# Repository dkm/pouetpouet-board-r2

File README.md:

# PouetPouet

The firmware is [Keyberon](https://github.com/TeXitoi/keyberon), a
pure rust firmware.

The goal was:
* build a custom keyboard from scratch
* continue to learn embedded rust
* have fun

## Features

 * ortholinear
 * 60 keys, using Cherry MX switches, only 1U keycaps;
 * 4 RGB LEDs for status;
 * 6 RGB LEDs for backlight;
 * USB-C connector;
 * 1 STM32F072 MCU, with hardware USB DFU bootloader;
 * Only onboard SMD component (except for the switches).
 * ESD protection

## Inspiration

 * [Keyseebee](https://github.com/TeXitoi/keyseebee) for being the «I will
   change it quickly and have something ready in an hour» base project (even if
   I ended up redoing most of the hardware design). It was really nice to have a
   solid base to learn and bootstrap the project.
 * [Typematrix 2030](http://typematrix.com/2030/features.php): I own 2 of them
   and really love them. But both are getting old and some keys are not working
   correctly (this motivated the keyboard change).
 * [Steamvan](https://github.com/jmdaly/steamvan) for some KiCad design ideas;
 * [Preonic](https://olkb.com/collections/preonic) as a model: ortholinear, good
   balance between size/usability, simple.

## Usefull resources
 * [Mechanical Keyboard](https://github.com/help-14/mechanical-keyboard) is a list of DIY keyboards
 * [Awesome Mechanical Keyboard](https://github.com/BenRoe/awesome-mechanical-keyboard) is another [«awesome»](https://github.com/topics/awesome) list
 * [Masterzen](http://www.masterzen.fr/2020/05/03/designing-a-keyboard-part-1/)
   and many others for writing online tutorials for newbies like me.

## Build log

Disclaimer: I'm a software developper, this is my first real PCB design and my first try at SMD soldering: do not take anything here for granted :)

The project started as a quick-hack of Keyseebee to make it simpler but ended up
as a near full redesign. As every DIY project, the goal was to be quick and
simple (spoiler: it was neither).

Half of the parts have been soldered with a soldering iron (TS80P), the other
half with hot air station. Clearly, with my [un]existing soldering skills, the
hot air is a huge win. But I think I would have simply spent more time by only
using the iron. Even the small sod-323 diodes without the `_handsoldering` pads
(mistake) were not a real problem (tricky, but even I could do it). For
reference, I have soldered all SMD components for the second board under 2 hours
with hot air.

The trickiest
part is the USB connector if you don't have a hot air station: the plastic
casing melts with the solder.

* The LEDs are mostly optional, and the 6 used for the backlight are nearly
  useless. I did not really study how to insert LEDs for a nice backlight and the
  result is not really satisfactory.
* I'll hopefully find time to use plexiglass plate to put below the PCB and
  above the visible part. I've added holes for this but never really planed
  anything really. If you really want something nice here, you may check this
  before.

## Layout

As a typematrix user, I really like the middle column with `backspace/enter/del`
so naturaly I've tried to do something similar. The [initial
layout](http://www.keyboard-layout-editor.com/##@_pcb:true%3B&@_c=%238f00ff&sm=cherry&sb=gateron%3B&=F2%0A%0A%0A%E2%80%94%0A%0A%0A%0A%0A%0A1%0A%22&=F3%0A%0A%0A%3C%0A%0A%0A%0A%0A%0A2%0A%C2%AB&=F4%0A%0A%0A%3E%0A%0A%0A%0A%0A%0A3%0A%C2%BB&=F5%0A%0A%0A%5B%0A%0A%0A%0A%0A%0A4%0A(&=F6%0A%0A%0A%5D%0A%0A%0A%0A%0A%0A5%0A)&_c=%23cf94ff%3B&=F1%0A%0A%0A%0A%0A%0A%0A%0A%0A%23%0A$&_c=%238f00ff%3B&=F7%0A%0A%0A%0A%0A%0A%0A%0A%0A6%0A%2F@&=F8%0A%0A%0A%0A%0A%0A%0A%0A%0A7%0A+&=F9%0A%0A%0A%0A%0A%0A%0A%0A%0A8%0A-&=F10%0A%0A%0A%0A%0A%0A%0A%0A%0A9%0A%2F%2F&=F11%0A%0A%0A%0A%0A%0A%0A%0A%0A0%0A*&_c=%23cf94ff%3B&=F12%0A%0A%0A%0A%0A%0A%0A%0A%0A%C2%B0%0A%2F=%3B&@_c=%234bfad0%3B&=PrtScr%0A%0A%0A%7C%0A%0A%0A%0A%0A%0AB&=VerNum%0A%0A%0A%0A%0A%0A%0A%0A%0A%C3%89&=%0A%0A%0A%2F&%0A%0A%0A%0A%0A%0AP&=%0A%0A%0A%C5%93%0A%0A%0A%0A%0A%0AO&_a:7%3B&=%C3%88&_c=%23fcc0c0&a:4%3B&=Esc%0A%0A%0A%0A%0A%0A%0A%0A%0ATab&_c=%23dbfff7%3B&=Ins%0A%0A%0A%0A%0A%0A%0A%0A%0A!%0A%5E&_c=%234bfad0%3B&=%2F&uArr%2F%3B%0A%0A%0A%0A%0A%0A%0A%0A%0AV&=%2F&dArr%2F%3B%0A%0A%0A%0A%0A%0A%0A%0A%0AD&=7%0A%0A%0A%0A%0A%0A%0A%0A%0AL&=8%0A%0A%0A%0A%0A%0A%0A%0A%0AJ&=9%0A%0A%0A%0A%0A%0A%0A%0A%0AZ%3B&@=%0A%0A%0A%C3%A6%0A%0A%0A%0A%0A%0AA&=%0A%0A%0A%C3%B9%0A%0A%0A%0A%0A%0AU&=%0A%0A%0A%22%0A%0A%0A%0A%0A%0AI&=%0A%0A%0A%E2%82%AC%0A%0A%0A%0A%0A%0AE&_c=%23dbfff7&a:5%3B&=%0A,%0A%0A%0A%0A%0A%2F%3B&_c=%23fcc0c0&a:7%3B&=%3Ci%20class%2F='mss%20mss-Unicode-BackSpace-DeleteLeft-Big-2'%3E%3C%2F%2Fi%3E&_c=%234bfad0&a:4%3B&=%3Ci%20class%2F='kb%20kb-Arrows-Top-2'%3E%3C%2F%2Fi%3E%0A%0A%0A%0A%0A%0A%0A%0A%0AC&=%2F&uarr%2F%3B%0A%0A%0A%0A%0A%0A%0A%0A%0AT&=%3Ci%20class%2F='kb%20kb-Arrows-Bottom-2'%3E%3C%2F%2Fi%3E%0A%0A%0A%0A%0A%0A%0A%0A%0AS&=4%0A%0A%0A%0A%0A%0A%0A%0A%0AR&=5%0A%0A%0A%0A%0A%0A%0A%0A%0AN&=6%0A%0A%0A%0A%0A%0A%0A%0A%0AM%3B&@=%C3%8A%0A%0A%0A%5C%0A%0A%0A%0A%0A%0A%C3%80&=%3Ci%20class%2F='fa%20fa-rotate-left'%3E%3C%2F%2Fi%3E%0A%0A%0A%7B%0A%0A%0A%0A%0A%0AY&=%3Ci%20class%2F='fa%20fa-plus'%3E%3C%2F%2Fi%3E%0A%0A%0A%7D%0A%0A%0A%0A%0A%0AX&_c=%23dbfff7%3B&=%3Ci%20class%2F='fa%20fa-minus'%3E%3C%2F%2Fi%3E%0A%0A%0A%E2%80%A6%0A%0A%0A%0A%0A%0A%2F:%0A.&_c=%234bfad0%3B&=%0A%0A%0A~%0A%0A%0A%0A%0A%0AK&_c=%23fcc0c0&a:7%3B&=%2F&crarr%2F%3B&_c=%23dbfff7&a:4%3B&=%2F&larr%2F%3B%0A%0A%0A%0A%0A%0A%0A%0A%0A%3F%0A'&_c=%234bfad0%3B&=%2F&darr%2F%3B%0A%0A%0A%0A%0A%0A%0A%0A%0AQ&=%2F&rarr%2F%3B%0A%0A%0A%0A%0A%0A%0A%0A%0AG&=1%0A%0A%0A%0A%0A%0A%0A%0A%0AH&=2%0A%0A%0A%0A%0A%0A%0A%0A%0AF&=3%0A%0A%0A%0A%0A%0A%0A%0A%0A%C3%87%3B&@_c=%23ff59d1&a:7%3B&=Ctrl&_c=%238f00ff%3B&=%2F&uArr%2F%3B&=Win&_c=%231500ff&a:4%3B&=%3Ci%20class%2F='fa%20fa-lightbulb-o'%3E%3C%2F%2Fi%3E%0A%0A%0A%0A%0A%0A%0A%0A%0AShift&_c=%238f00ff&a:7%3B&=Alt&_c=%23fcc0c0&a:4%3B&=%0A%0A%0A%2F_%0A%0A%0A%0A%0A%0Anbspc%0Aspc&_c=%238f00ff&a:7%3B&=AltGr&_c=%234bfad0&a:4%3B&=0%0A%0A%0A%0A%0A%0A%0A%0A%0AW&_c=%23dbfff7&a:5%3B&=%0A%25%0A%0A%0A%0A%0A%60&_c=%238f00ff&a:7%3B&=Del&_c=%231500ff%3B&=Shift&_c=%23ff59d1%3B&=Ctrl) has only the `%` and `w` key at different locations:

You can also see how the LEDs are currently used. It's mostly useless/for fun. They may be used someday to measure typing speed or do something else, but in the meantime, they blink like this:

## Bill Of Materials

|Item                                                                      |Package|Qty|Remarks                                |Price |
|--------------------------------------------------------------------------|-------|--:|---------------------------------------|-----:|
| PCB                                                                      |       | 1 | [aisler](https://aisler.net/p/BWUOMHHS) (by 3 mini) |  28.80€  |
| 100 nF                                                                   | 0805  | 5 |  aisler*                                 | 0€    |
| PRTR5V0U2X,215                                                           | sot-143| 1 | aisler*                                 | 0.43€ |
| 4.7 uF                                                                   | 0805  | 2 |  aisler*                                 | 0€    |
| 470 Ohm                                                                  | 0805  | 1 |  aisler*                                 | 0€    |
| TLV70233DBVR                                                             | sot-23| 1 |  aisler*                                 | 0.37€ |
| 74LVC1G34GW,125                                                          |       | 1 |  aisler*                                 | 0.28€ |
| 0805L050WR (500mA Polyfuse)                                              | 0805  | 1 |  aisler*                                 | 1.91€ |
| RS282G05A3SMRT (micro switch)                                            |       | 2 |  aisler*                                 | 1.26€ |
| 100nF                                                                    | 0805  | 2 |  aisler*                                 | 0€ |
| 5.1 kOhm                                                                 | 0805  | 3 |  aisler*                                 | 0€ |
| 0805L050WR (500mA Polyfuse)                                              | 0805  | 1 |  aisler*                                 | 0€ |
| [1N4148WS-7-F](https://fr.rs-online.com/web/p/diodes-de-commutation/7384737/) | sod-323 | 60|   rs-online (by 200)                  | 3.24€  |
| [WS2812B](https://www.aliexpress.com/item/4000750610574.html?spm=a2g0s.9042311.0.0.27424c4dS3DGkH) |       | 10|                                       | 1€  |
| [USB TypeC HRO Receptacle](https://www.aliexpress.com/item/33056042016.html?spm=a2g0s.9042311.0.0.1d8b4c4d8WcR7j) |       | 1 |  by 10 mini   | 0.25€  |
| [Gateron Switch 5-pin](https://fr.aliexpress.com/item/32797603005.html?spm=a2g0s.9042311.0.0.72906c37zAMdzk) |       | 60| by 65                                   | 15.24€ |
| [Blank DSA Keycaps](https://fr.aliexpress.com/item/32850729893.html?spm=a2g0s.9042311.0.0.3c4b6c37vkQ3vr)    |       | 60| by 200                                   | 15.6€  |
| [STM32F072CBT6](https://fr.aliexpress.com/item/4000419148272.html?spm=a2g0s.9042311.0.0.43286c37wfyZHW)      | LQFP48 | 1 |                                         | 2.87€ | 
|--------------------------------------------------------------------------|-------|--:|------------------------------------------|------|
|[TPS2553DBVR-1](https://www.digikey.fr/fr/products/detail/texas-instruments/TPS2553DBVR-1/5143873) | PKG? | 1 | FIND | ??€|
|[SK6812-Mini]() | PGK? | 60+4 | FIND | ??€ |
| 100nF                                                                    | 0805  | 2 |  aisler*                                 | 0€ |
| 9.1 kOhm                                                                 | 0805  | 4 |  aisler*                                 | 0€ |
| 68 kOhm                                                                  | 0805  | 6 |  aisler*                                 | 0€ |
|[2N7002](https://www.digikey.fr/fr/products/detail/stmicroelectronics/2N7002/654418) | SOT23-3 | 2 | FIND | ?€ |
| 100uF  | 6032 | 1 | FIND | ??€ |

The total for 3 keyboard is 71.25€. Beware that some parts can't be ordered for
the exact amount and you need to buy more (in particular, aisler won't do
anything under 3 units, so you need to spend at least ~90€ for 3 PCBs).

*: Bought using magic match from Aisler. Some components are then
 «free» (resistor, capacitor) and some are not.

## Compiling and flashing

Install the complete toolchain and utils:

```shell
curl https://sh.rustup.rs -sSf | sh
rustup target add thumbv6m-none-eabi
rustup component add llvm-tools-preview
cargo install cargo-binutils
sudo apt-get install dfu-util
```

Compile:

Do not omit the `--release` as the debug code will not fit in the memory (the
linker will raise an error).

```shell
cd firmware
cargo objcopy --bin pouetpouet --release -- -O binary pouetpouet.bin
```

To flash using dfu-util, first put the board in dfu mode by pressing
BOOT, pressing and releasing RESET and releasing BOOT. Then:

```shell
dfu-util -d 0483:df11 -a 0 -s 0x08000000:leave -D pouetpouet.bin
```

The fist time, if the write fail, your flash might be protected. To
unprotect:

```shell
dfu-util -d 0483:df11 -a 0 -s 0x08000000:force:unprotect -D pouetpouet.bin
```

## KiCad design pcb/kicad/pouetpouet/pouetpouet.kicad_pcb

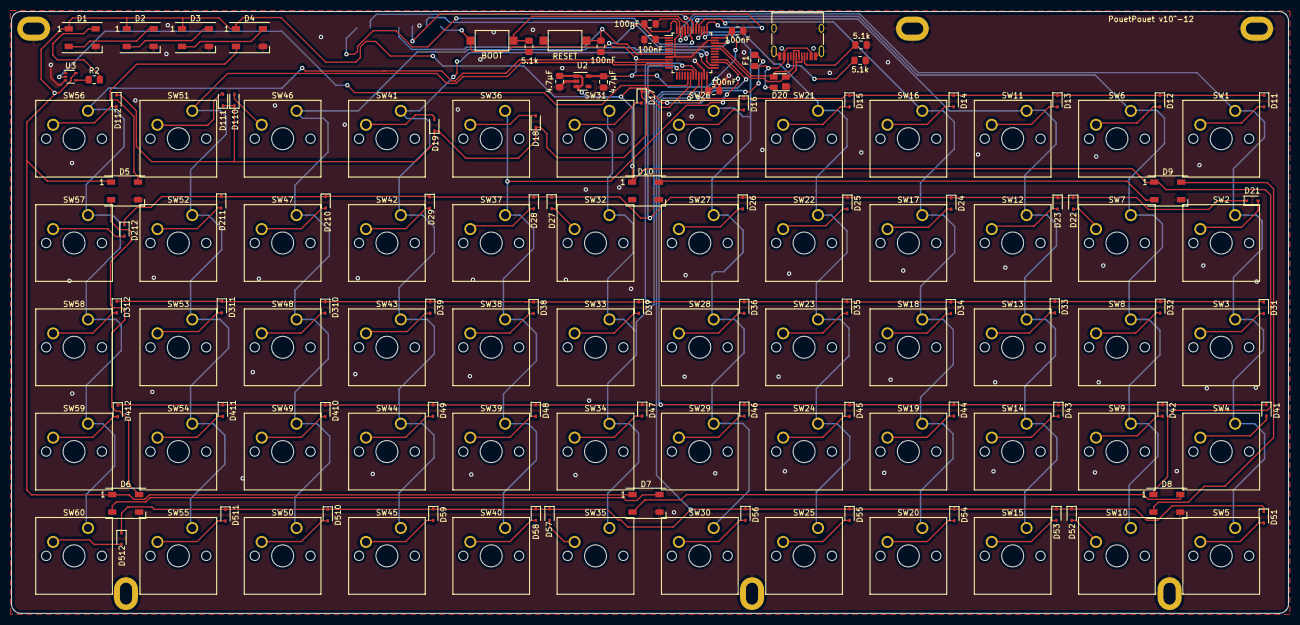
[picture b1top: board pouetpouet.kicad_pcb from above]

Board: 2 copper layers, 232.6 x 109.6 mm, 156 parts (1 on the bottom side), 103 nets.

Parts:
C1, C2, C3, C4, C5: 100nF; C_0805_2012Metric_Pad1.15x1.40mm_HandSolder
C6, C7: 4.7µF; C_0805_2012Metric_Pad1.15x1.40mm_HandSolder
D1, D2, D3, D4, D5, D6, D7, D8, D9, D10: WS2812B; LED_WS2812B_PLCC4_5.0x5.0mm_P3.2mm
D11: D1.1; D_SOD-323
D12: D1.2; D_SOD-323
D13: D1.3; D_SOD-323
D14: D1.4; D_SOD-323
D15: D1.5; D_SOD-323
D16: D1.6; D_SOD-323
D17: D1.7; D_SOD-323
D18: D1.8; D_SOD-323
D19: D1.9; D_SOD-323
D20: PRTR5V0U2X; SOT-143
D21: D2.1; D_SOD-323
D22: D2.2; D_SOD-323
D23: D2.3; D_SOD-323
D24: D2.4; D_SOD-323
D25: D2.5; D_SOD-323
D26: D2.6; D_SOD-323
D27: D2.7; D_SOD-323
D28: D2.8; D_SOD-323
D29: D2.9; D_SOD-323
D31: D3.1; D_SOD-323
D32: D3.2; D_SOD-323
D33: D3.3; D_SOD-323
D34: D3.4; D_SOD-323
D35: D3.5; D_SOD-323
D36: D3.6; D_SOD-323
D37: D3.7; D_SOD-323
D38: D3.8; D_SOD-323
D39: D3.9; D_SOD-323
D41: D4.1; D_SOD-323
D42: D4.2; D_SOD-323
D43: D4.3; D_SOD-323
D44: D4.4; D_SOD-323
D45: D4.5; D_SOD-323
D46: D4.6; D_SOD-323
D47: D4.7; D_SOD-323
D48: D4.8; D_SOD-323
D49: D4.9; D_SOD-323
D51: D5.1; D_SOD-323
D52: D5.2; D_SOD-323
D53: D5.3; D_SOD-323
D54: D5.4; D_SOD-323
D55: D5.5; D_SOD-323
D56: D5.6; D_SOD-323
D57: D5.7; D_SOD-323
D58: D5.8; D_SOD-323
D59: D5.9; D_SOD-323
D110: D1.10; D_SOD-323
D111: D1.11; D_SOD-323
D112: D1.12; D_SOD-323
D210: D2.10; D_SOD-323
D211: D2.11; D_SOD-323
D212: D2.12; D_SOD-323
D310: D3.10; D_SOD-323
D311: D3.11; D_SOD-323
D312: D3.12; D_SOD-323
D410: D4.10; D_SOD-323
D411: D4.11; D_SOD-323
D412: D4.12; D_SOD-323
D510: D5.10; D_SOD-323
D511: D5.11; D_SOD-323
D512: D5.12; D_SOD-323
F1: 500mA; R_0805_2012Metric_Pad1.15x1.40mm_HandSolder
H1, H2, H3, H4, H5, H6: MountingHole_Pad; MountingHole_2.2mm_M2_Pad
J1: USB_C_Receptacle_USB2.0; USB_C_Receptacle_HRO_TYPE-C-31-M-12
J3: Conn_01x07_Male; Harwin_M20-89007xx_1x07_P2.54mm_Horizontal
R1, R6, R7: 5.1k; R_0805_2012Metric_Pad1.15x1.40mm_HandSolder
R2: 470; R_0805_2012Metric_Pad1.15x1.40mm_HandSolder
SW1, SW2, SW3, SW4, SW5, SW6, SW7, SW8, SW9, SW10, SW11, SW12, SW13, SW14, SW15, SW16, SW17, SW18, SW19, SW20, SW21, SW22, SW23, SW24, SW25, SW26, SW27, SW28, SW29, SW30, SW31, SW32, SW33, SW34, SW35, SW36, SW37, SW38, SW39, SW40, SW41, SW42, SW43, SW44, SW45, SW46, SW47, SW48, SW49, SW50, SW51, SW52, SW53, SW54, SW55, SW56, SW57, SW58, SW59, SW60: SW_Push; SW_Cherry_MX_1.00u_PCB
SWBOOT1: BOOT; SW_SPST_CK_RS282G05A3
SWRST1: RESET; SW_SPST_CK_RS282G05A3
U1: STM32; LQFP-48_7x7mm_P0.5mm
U2: TLV70233_SOT23-5; SOT-23-5
U3: 74LVC1G34; SOT-353_SC-70-5

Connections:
+3V3: C2.2, C3.2, C4.2, C5.2, C6.2, J3.1, SWBOOT1.2, U1.1, U1.9, U1.24, U1.36, U1.48, U2.5
+5V: C7.2, D1.1, D2.1, D3.1, D4.1, D5.1, D6.1, D7.1, D8.1, D9.1, D10.1, F1.2, U2.1, U2.3, U3.5
COL1: SW1.1, SW2.1, SW3.1, SW4.1, SW5.1, U1.46
COL2: SW6.1, SW7.1, SW8.1, SW9.1, SW10.1, U1.45
COL3: SW11.1, SW12.1, SW13.1, SW14.1, SW15.1, U1.41
COL4: SW16.1, SW17.1, SW18.1, SW19.1, SW20.1, U1.40
COL5: SW21.1, SW22.1, SW23.1, SW24.1, SW25.1, U1.39
COL6: SW26.1, SW27.1, SW28.1, SW29.1, SW30.1, U1.38
COL7: SW31.1, SW32.1, SW33.1, SW34.1, SW35.1, U1.28
COL8: SW36.1, SW37.1, SW38.1, SW39.1, SW40.1, U1.27
COL9: SW41.1, SW42.1, SW43.1, SW44.1, SW45.1, U1.25
COL10: SW46.1, SW47.1, SW48.1, SW49.1, SW50.1, U1.26
COL11: SW51.1, SW52.1, SW53.1, SW54.1, SW55.1, U1.11
COL12: SW56.1, SW57.1, SW58.1, SW59.1, SW60.1, U1.10
D+: D20.3, J1.A6, J1.B6, U1.33
D-: D20.2, J1.A7, J1.B7, U1.32
GND: C1.1, C2.1, C3.1, C4.1, C5.1, C6.1, C7.1, D1.3, D2.3, D3.3, D4.3, D5.3, D6.3, D7.3, D8.3, D9.3, D10.3, D20.1, H1.1, H2.1, H3.1, H4.1, H5.1, H6.1, J1.A1, J1.A12, J1.B1, J1.B12, J1.S1, J3.5, R1.2, R6.2, R7.2, SWRST1.1, U1.8, U1.23, U1.35, U1.47, U2.2, U3.3
NRST: C1.2, J3.4, SWRST1.2, U1.7
unnamed: D1.2, D2.4
unnamed: D1.4, R2.2
unnamed: D2.2, D3.4
unnamed: D3.2, D4.4
unnamed: D4.2, D5.4
unnamed: D5.2, D6.4
unnamed: D6.2, D7.4
unnamed: D7.2, D8.4
unnamed: D8.2, D9.4
unnamed: D9.2, D10.4
unnamed: D11.2, SW1.2
unnamed: D12.2, SW6.2
unnamed: D13.2, SW11.2
unnamed: D14.2, SW16.2
unnamed: D15.2, SW21.2
unnamed: D16.2, SW26.2
unnamed: D17.2, SW31.2
unnamed: D18.2, SW36.2
unnamed: D19.2, SW41.2
unnamed: D21.2, SW2.2
unnamed: D22.2, SW7.2
unnamed: D23.2, SW12.2
unnamed: D24.2, SW17.2
unnamed: D25.2, SW22.2
unnamed: D26.2, SW27.2
unnamed: D27.2, SW32.2
unnamed: D28.2, SW37.2
unnamed: D29.2, SW42.2
unnamed: D31.2, SW3.2
unnamed: D32.2, SW8.2
unnamed: D33.2, SW13.2
unnamed: D34.2, SW18.2
unnamed: D35.2, SW23.2
unnamed: D36.2, SW28.2
unnamed: D37.2, SW33.2
unnamed: D38.2, SW38.2
unnamed: D39.2, SW43.2
unnamed: D41.2, SW4.2
unnamed: D42.2, SW9.2
unnamed: D43.2, SW14.2
unnamed: D44.2, SW19.2
unnamed: D45.2, SW24.2
unnamed: D46.2, SW29.2
unnamed: D47.2, SW34.2
unnamed: D48.2, SW39.2
unnamed: D49.2, SW44.2
unnamed: D51.2, SW5.2
unnamed: D52.2, SW10.2
unnamed: D53.2, SW15.2
unnamed: D54.2, SW20.2
unnamed: D55.2, SW25.2
unnamed: D56.2, SW30.2
unnamed: D57.2, SW35.2
unnamed: D58.2, SW40.2
unnamed: D59.2, SW45.2
unnamed: D110.2, SW46.2
unnamed: D111.2, SW51.2
unnamed: D112.2, SW56.2
unnamed: D210.2, SW47.2
unnamed: D211.2, SW52.2
unnamed: D212.2, SW57.2
unnamed: D310.2, SW48.2
unnamed: D311.2, SW53.2
unnamed: D312.2, SW58.2
unnamed: D410.2, SW49.2
unnamed: D411.2, SW54.2
unnamed: D412.2, SW59.2
unnamed: D510.2, SW50.2
unnamed: D511.2, SW55.2
unnamed: D512.2, SW60.2
unnamed: J1.A5, R7.1
unnamed: J1.B5, R6.1
unnamed: R1.1, SWBOOT1.1, U1.44
unnamed: R2.1, U3.4
ROW1: D11.1, D12.1, D13.1, D14.1, D15.1, D16.1, D17.1, D18.1, D19.1, D110.1, D111.1, D112.1, U1.18
ROW2: D21.1, D22.1, D23.1, D24.1, D25.1, D26.1, D27.1, D28.1, D29.1, D210.1, D211.1, D212.1, U1.19
ROW3: D31.1, D32.1, D33.1, D34.1, D35.1, D36.1, D37.1, D38.1, D39.1, D310.1, D311.1, D312.1, U1.20
ROW4: D41.1, D42.1, D43.1, D44.1, D45.1, D46.1, D47.1, D48.1, D49.1, D410.1, D411.1, D412.1, U1.21
ROW5: D51.1, D52.1, D53.1, D54.1, D55.1, D56.1, D57.1, D58.1, D59.1, D510.1, D511.1, D512.1, U1.22
SPI1_MOSI_PA7: U1.17, U3.2
SWDCLK: J3.3, U1.37
SWDIO: J3.2, U1.34
U1_RX_PB7: J3.7, U1.43
U1_TX_PB6: J3.6, U1.42
VCC: D20.4, F1.1, J1.A4, J1.A9, J1.B4, J1.B9

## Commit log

2020-11-11 Update README with more acurate info
2020-11-11 Use type to make code easier to read
2020-11-11 Initial work for Pouetpouet board
    Based on keyseebee but now very different.
2020-11-11 Modified the bépo layout a bit
    Moved few keys around:
    - swapped w and AltGr.
    - swapped Raise and Shift
    - added ê/Ê
2020-11-11 Update BOM with correct parts, vendor and price.
2020-12-17 Update code after keyberon update
    Simply port current firmware. No CustomAction yet.
2021-01-10 Simple backlight support using custom actions.
    Use keyberon's custom action to create some useless LEDs mode.
    Frequency (when applicable) and color can be changed by some keypress.
2021-01-10 Allow for minor version change in dependencies
2021-01-12 Add sample gif for showing LEDs, refresh layout
    Update layout with latest changes (and add LEDs control keys).
2021-01-15 Add a simple LED bleep at start
    Always friendly to have a feedback from the device after it has booted.
2021-01-16 Change Keyboard::leds to leds_mut following upstream change.
    The function changed names while upstreaming it.
    Reverting back keyberon to upstream git instead following this change.
2021-01-22 Fix layout image
    F1->F6 were wrongly labeled (actual layout is correct, only the image was not)
2021-01-22 Refresh Cargo.lock after update
2021-01-22 Minor change in layout
    Add Volume keys and also map page-up/down on the 2 keys in lower-right corner
    for easier access (more similar to Typematrix, very convenient for reading).
2021-02-10 Update README.md
    Remove duplicated list of existing keyboards.
2021-05-19 Update dependencies
2021-05-19 Use new macro to define layers + cleaning
    Use the new layout!() macro for easier and more readable layers definitions.
    Add a testmode feature, used to have 'a' on all keys, easier to test if all
    switch are correctly working or not.
    Also fixed some minor warnings.
2021-05-19 Add nyan-keeb picture
2021-05-20 Add simple CAD file for plate
    Initial plate design for early test/prototype.
2022-02-25 Update some dependencies
2022-02-26 Bump cortex-m* dep version
2022-02-26 Minor code cleaning
    Remove some warnings, apply clippy hints.
2022-03-01 Add cargo-embed configuration
    Flash + gdb server
2022-05-09 update kicad footprints repos
2022-05-09 Update to KiCad 6.0
    Simply open and save the SCH and PCB to convert them to KiCad 6.0.
    No checks done on the result.
2022-06-15 New revision for PouetPouet board
    What is changing:
    - Cherry-MX hotswap sockets for all 60 switches
    - Per switch RGB LED (SK6812-MiniE)
    What is not changing:
    - Size (exact same board cutout)
    - overall components (mcu stmf072)
2022-07-22 Rev 2.1 for error with sk6812mini-e
    The symbol used for the mini-e is the mini one. Pins numbering for both parts
    are NOT the same: leads to non functionnal keys backlight.
    This changes:
    - fixes this error
    - make the OSHW logo nicer (copper instead of silk)
    The symbol used for mini-e comes from the Djinn keyboard.
2022-07-22 rust: extract layout in separate module
    First step towards reusing for pouetpouet-r2: split!
2022-07-22 rust: update to latest keyberon
    Handle some change in action/custom action handling.
2022-07-22 Initial Ada firmware
    Missing doc, comment.
2022-07-22 rust: Initial hold tap work
    Currently not working (Tap action is never triggered unless some other
    keys is tapped simultaneous).
2022-07-22 Update all crate, in particular rtic
    Keyboard works, but customevents for leds are not working (yet).
2022-07-22 Move rust firmware in subdir
    ... for the upcoming Ada one.
2022-07-22 Initial support for Layers
    Click now support Layers, so port some more layout from the existing
    rust firmware.
2022-07-22 Update GPIO for rev2 board
2022-07-27 pcb: minor tuning of GND plane
    Tune GND plane + moved minor tracks.
2022-07-30 pcb: apply rules, fix last warning
    Add more PWR track for one led
    RC for 2.1
2022-08-28 ada: build stm32 hal in dev mode
    In release mode the mcu crashes very quickly, there must be some UB somewhere...
2022-08-28 rust: missing capslock
    Just realized the layout doesn't have this useless key.
    Was stuck with CAPSLOCK set because of an external glitch and couldn't clear it.
2022-08-28 ada: initial support for timing
    Use clock configuration (only HSE48 for now) and use timer to have a 1ms update
    frequency.
2022-08-28 ada: modifiers, layers and regular keys are working
    Still need to add timings as currently the processor is looping full speed,
    which may cause some lost events as the USB only polls at the frequency
    advertised in the descriptor (few ms).
2022-09-04 rust: use holdtap keys
    Make i-e-t keys (bépo) alt-l1-alt with holdtap
2022-09-08 rust: initial support for keys LED matrix
    LEDs are set/clear for press/release events.
2022-09-09 rust: try to use custom event to change color
    TLDR; needs a redesign for correctly sharing LEDS (in usb_class) and lower prio
    data in `backlight`.
2023-01-20 rust: Add tap_hold interval
    HoldTap don't play well with games where you may need to hold down some keys
    without triggering the layer change.
2023-01-20 rust: update dependencies, adjust Keyberon usage
    Do a "cargo update" and adjust the minor change in Keyberon.
2023-10-26 cad: adjust plate
    Fix the switch size from 19 to 19.05 to match actual footprint.
2024-01-24 cad: wip on plate
    Add screw holes.
2024-01-25 cad: adjust M2 screw holes
2024-02-09 cad: adjust M2 holes in plate
    Previous holes were a bit too large after printing: standoffs are a
    bit smaller and fall through the plate.
2024-02-17 cad: adjust (again) plate holes size
    Previous adjustements were not enough, standoff are still too thin.
    Enlarge a bit switch holes to avoid having to force the switches in.
2024-02-21 cad: fix M2 hole
    By default, circle() takes the radius, not the diameter. No surprises
    the holes were too large.
